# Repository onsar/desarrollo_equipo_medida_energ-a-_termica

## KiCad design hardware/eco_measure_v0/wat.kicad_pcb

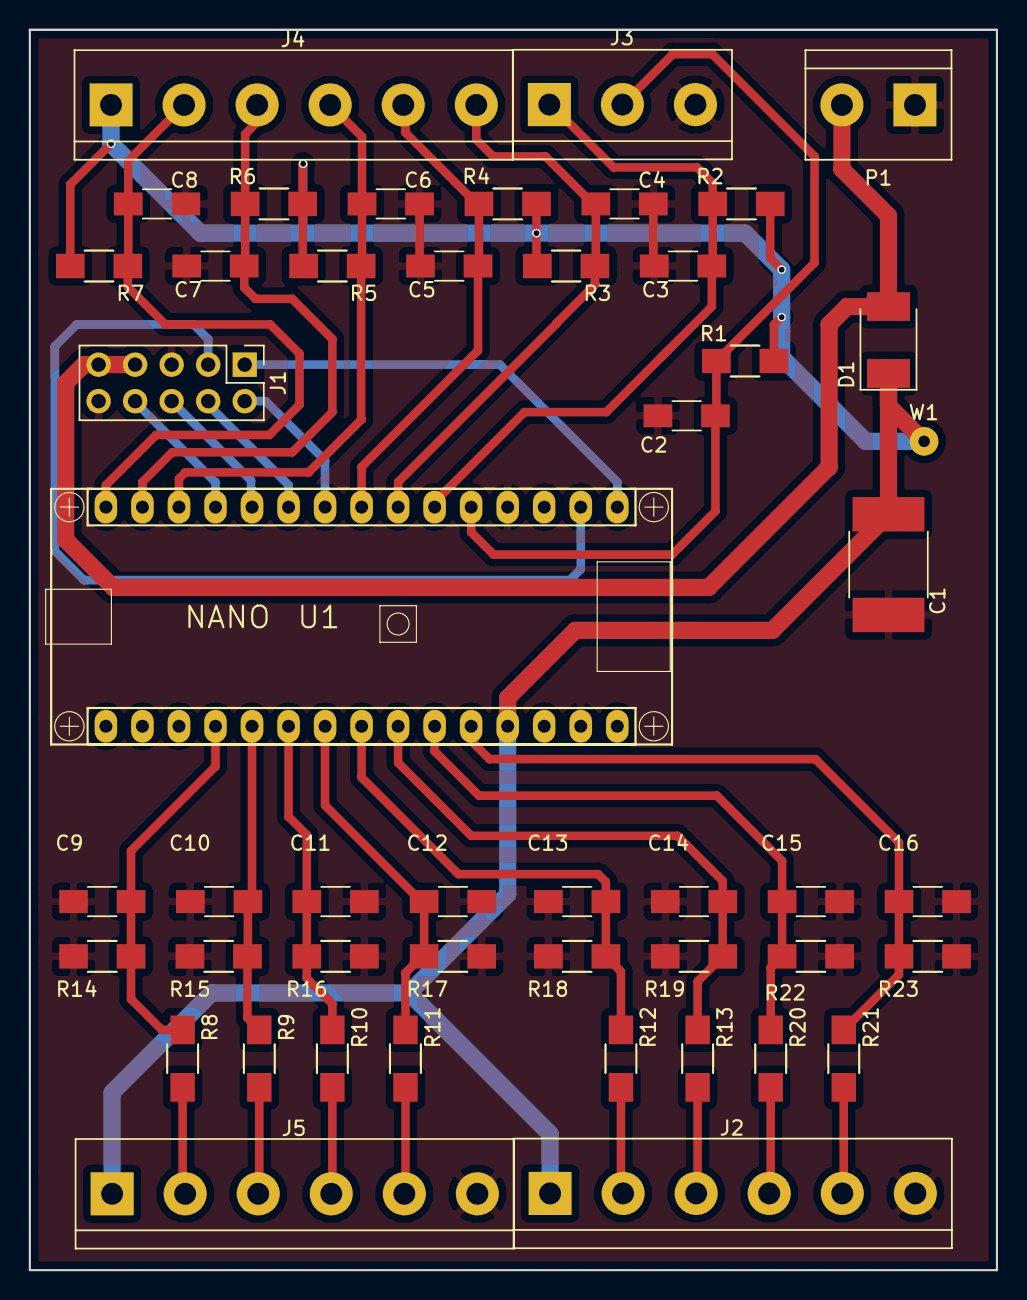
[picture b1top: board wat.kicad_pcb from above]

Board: 2 copper layers, 67.2 x 86.2 mm, 48 parts (0 on the bottom side), 32 nets.

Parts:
C1: 10uF; C_2220_HandSoldering
C2, C3, C4, C5, C6, C7, C8, C9, C10, C11, C12, C13, C14, C15, C16: 100nF; C_1206_HandSoldering
D1: schottky; D_2114
J1: Conn_02x05_Odd_Even; Pin_Header_Straight_2x05_Pitch2.54mm_onsar
J2, J4, J5: Conn_01x06; TerminalBlock_bornier-6_P5.08mm
J3: Conn_01x03; TerminalBlock_bornier-3_P5.08mm
P1: V_IN; TerminalBlock_bornier-2_P5.08mm
R1, R2, R3, R4, R5, R6, R7, R8, R9, R10, R11, R12, R13, R14, R15, R16, R17, R18, R19, R20, R21, R22, R23: 10k; R_1206_HandSoldering
U1: NANO; arduino_nano
W1: +5V; SolderWirePad_single_0-8mmDrill

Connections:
/A0: C9.1, R8.1, R14.2, U1.19
/A1: C10.1, R9.1, R15.2, U1.20
/A2: C11.1, R10.1, R16.2, U1.21
/A3: C12.1, R11.1, R17.2, U1.22
/A4: C13.1, R12.1, R18.2, U1.23
/A5: C14.1, R13.1, R19.2, U1.24
/A6: C15.1, R20.1, R22.2, U1.25
/A7: C16.1, R21.1, R23.2, U1.26
/D2: C2.1, J3.2, R1.1, U1.5
/D3: C3.1, J3.1, R2.1, U1.6
/D4: C4.1, J4.6, R3.1, U1.7
/D5: C5.1, J4.5, R4.1, U1.8
/D6: J1.2, U1.9
/D7: J1.4, U1.10
/D8: J1.6, U1.11
/D9: J1.8, U1.12
/D10: C6.1, J4.4, R5.1, U1.13
/D11: C7.1, J4.3, R6.1, U1.14
/D12: C8.1, J4.2, R7.1, U1.15
/ard_rx: J1.3, U1.2
/ard_tx: J1.1, U1.1
/jA0: J5.2, R8.2
/jA1: J5.3, R9.2
/jA2: J5.4, R10.2
/jA3: J5.5, R11.2
/jA4: J2.2, R12.2
/jA5: J2.3, R13.2
/jA6: J2.4, R20.2
/jA7: J2.5, R21.2
/vcc_5v: D1.2, J1.7, J1.9, P1.2
GND: C1.2, C2.2, C3.2, C4.2, C5.2, C6.2, C7.2, C8.2, C9.2, C10.2, C11.2, C12.2, C13.2, C14.2, C15.2, C16.2, J1.5, J1.10, J2.6, J3.3, J5.6, P1.1, R14.1, R15.1, R16.1, R17.1, R18.1, R19.1, R22.1, R23.1, U1.4, U1.29
VCC: C1.1, D1.1, J2.1, J4.1, J5.1, R1.2, R2.2, R3.2, R4.2, R5.2, R6.2, R7.2, U1.27, W1.1

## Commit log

2020-12-24 prueba de tiempos de 18b20
2020-12-28 version de temperatura fincionando 18b20matriz3
2020-12-29 18b20matriz3: vession operativa con el bucle global
2020-12-30 version operativa 18b20 & pcint
2021-01-02 version operativa pcint & 18b20 & Analogica
2021-01-02 desarrollando hw de ecoMeasure
2021-01-03 hacia la medida continua
2021-01-03 desarrollando el hardware
2021-01-05 avanzando en la medida continua y la PCB
2021-01-06 version operativa. Medida analogica, temperatura y caudal
2021-01-06 avanzando en el diseño de la pcb
2021-01-09 sw operativo. Organizando el código
2021-01-10 vesion funcional: avanzando en la limpieza del código
2021-01-10 hw version operativa completa
2021-01-18 cambio de d13 por d5
2021-01-22 PCB para fabricar
2021-02-04 software compatible con el hw definitivo
2021-02-07 mejoras contador_pcint_h
